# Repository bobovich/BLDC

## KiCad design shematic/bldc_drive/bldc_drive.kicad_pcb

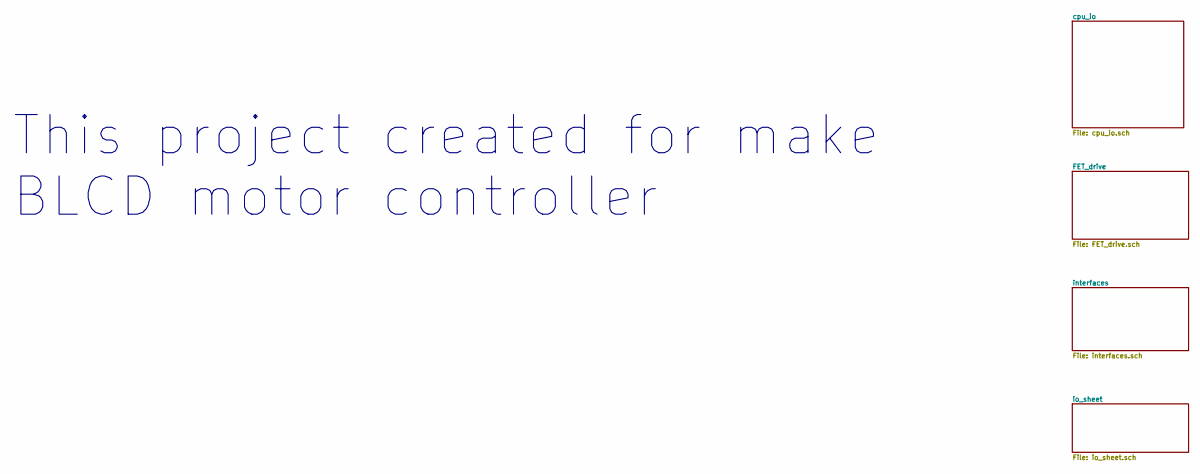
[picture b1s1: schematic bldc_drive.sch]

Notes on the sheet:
This project created for make BLCD motor controller

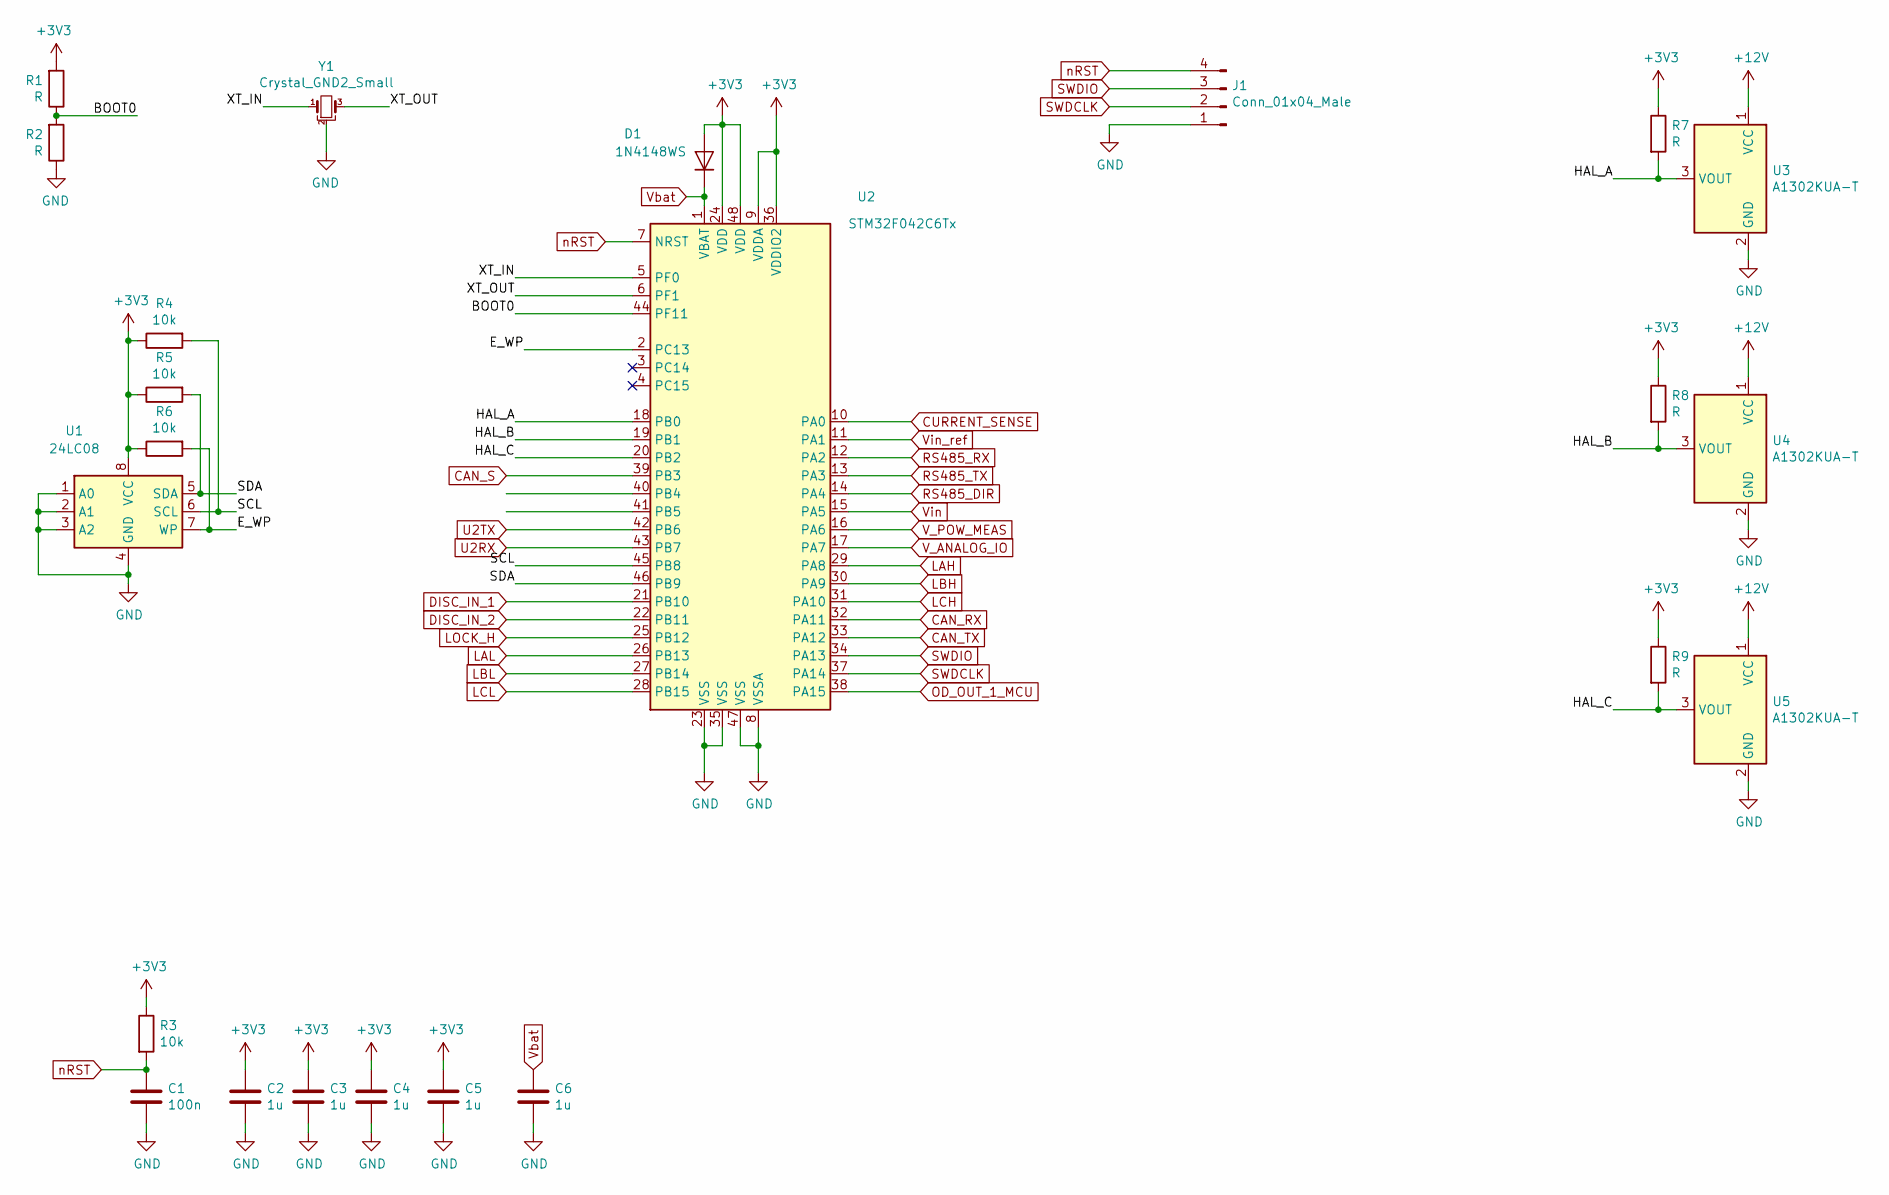
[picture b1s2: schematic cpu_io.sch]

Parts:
C1: 100n; C_0603_1608Metric
C2, C3, C4, C5, C6: 1u; C_0603_1608Metric
D1: 1N4148WS; D_SOD-123
J1: Conn_01x04_Male; PinHeader_1x04_P1.00mm_Vertical
R1, R2, R7, R8, R9: R; R_0603_1608Metric
R3, R4, R5, R6: 10k; R_0603_1608Metric
U1: 24LC08; SOIC-8_3.9x4.9mm_P1.27mm
U2: STM32F042C6Tx; LQFP-48_7x7mm_P0.5mm
U3, U4, U5: A1302KUA-T; TO-92_Wide
Y1: Crystal_GND2_Small; Resonator_SMD_muRata_CSTxExxV-3Pin_3.0x1.1mm

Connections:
+3V3: C2.2, C3.2, C4.2, C5.2, D1.2 (A), R1.2, R3.1, R4.1, R5.1, R6.1, R7.1, R8.1, R9.1, U1.8 (VCC), U2.9 (VDDA), U2.24 (VDD), U2.36 (VDDIO2), U2.48 (VDD); also elsewhere on the board
+12V: U3.1 (VCC), U4.1 (VCC), U5.1 (VCC); also elsewhere on the board
/cpu_io/BOOT0: R1.1, R2.2, U2.44 (PF11)
/cpu_io/E_WP: R6.2, U1.7 (WP), U2.2 (PC13)
/cpu_io/HAL_A: R7.2, U2.18 (PB0), U3.3 (VOUT)
/cpu_io/HAL_B: R8.2, U2.19 (PB1), U4.3 (VOUT)
/cpu_io/HAL_C: R9.2, U2.20 (PB2), U5.3 (VOUT)
/cpu_io/SCL: R4.2, U1.6 (SCL), U2.45 (PB8)
/cpu_io/SDA: R5.2, U1.5 (SDA), U2.46 (PB9)
/cpu_io/XT_IN: U2.5 (PF0), Y1.1
/cpu_io/XT_OUT: U2.6 (PF1), Y1.3
CAN_RX: U2.32 (PA11); also elsewhere on the board
CAN_S: U2.39 (PB3); also elsewhere on the board
CAN_TX: U2.33 (PA12); also elsewhere on the board
CURRENT_SENSE: U2.10 (PA0); also elsewhere on the board
GND: C1.1, C2.1, C3.1, C4.1, C5.1, C6.1, J1.1, R2.1, U1.1 (A0), U1.2 (A1), U1.3 (A2), U1.4 (GND), U2.8 (VSSA), U2.23 (VSS), U2.35 (VSS), U2.47 (VSS), U3.2 (GND), U4.2 (GND), U5.2 (GND), Y1.2; also elsewhere on the board
LAH: U2.29 (PA8); also elsewhere on the board
LAL: U2.26 (PB13); also elsewhere on the board
LBH: U2.30 (PA9); also elsewhere on the board
LBL: U2.27 (PB14); also elsewhere on the board
LCH: U2.31 (PA10); also elsewhere on the board
LCL: U2.28 (PB15); also elsewhere on the board
LOCK_H: U2.25 (PB12); also elsewhere on the board
RS485_DIR: U2.14 (PA4); also elsewhere on the board
RS485_RX: U2.12 (PA2); also elsewhere on the board
RS485_TX: U2.13 (PA3); also elsewhere on the board
SWDCLK: J1.2, U2.37 (PA14)
SWDIO: J1.3, U2.34 (PA13)
U2RX: U2.43 (PB7); also elsewhere on the board
U2TX: U2.42 (PB6); also elsewhere on the board
V_POW_MEAS: U2.16 (PA6); also elsewhere on the board
Vbat: C6.2, D1.1 (K), U2.1 (VBAT)
Vin: U2.15 (PA5); also elsewhere on the board
Vin_ref: U2.11 (PA1); also elsewhere on the board
nRST: C1.2, J1.4, R3.2, U2.7 (NRST)

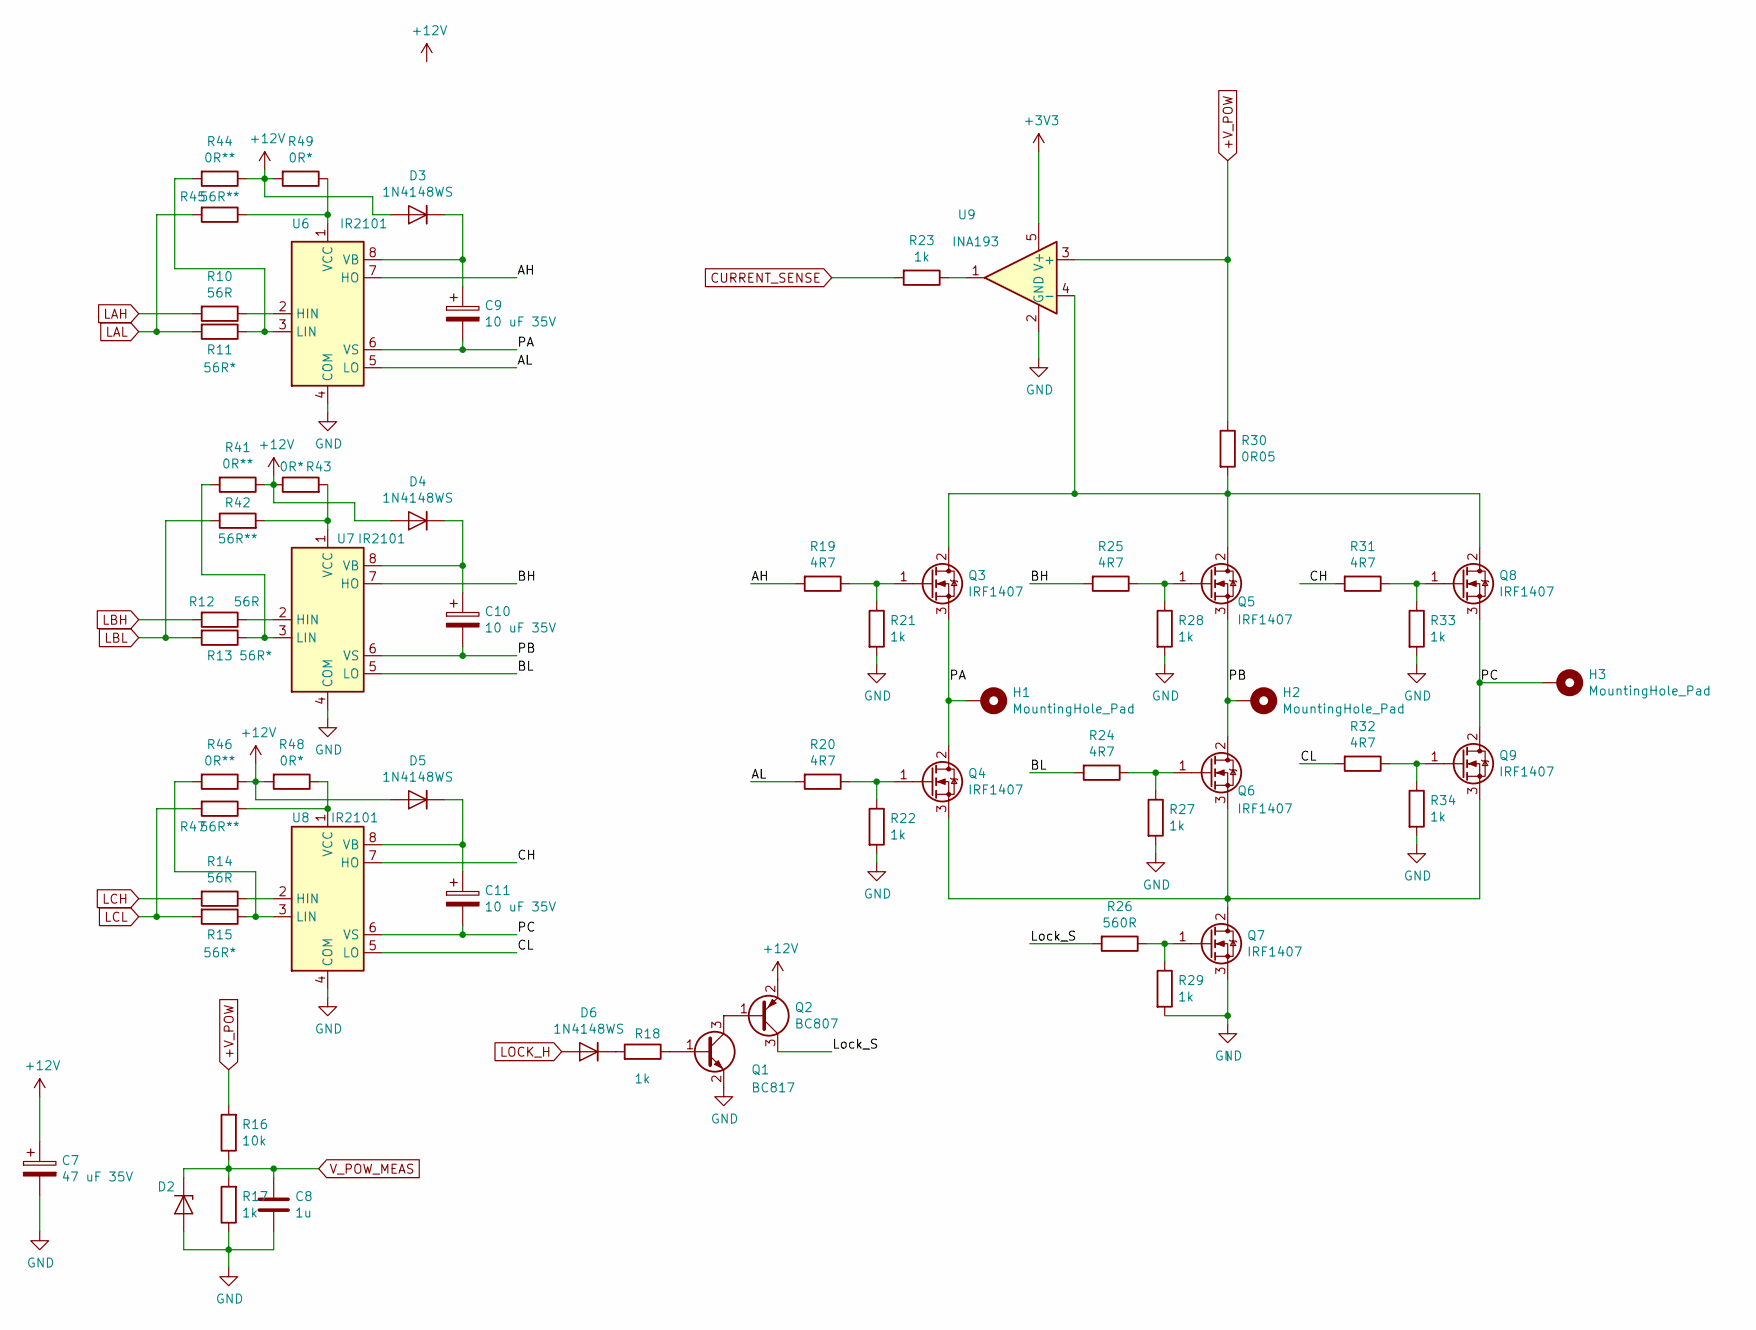
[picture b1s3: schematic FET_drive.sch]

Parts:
C7: 47 uF 35V; C_1206_3216Metric
C8: 1u; C_0805_2012Metric
C9, C10, C11: 10 uF 35V; C_1206_3216Metric
D2: DZ2S033X0L; D_SOD-523
D3, D4, D5, D6: 1N4148WS; D_SOD-123
H1, H2, H3: MountingHole_Pad; MountingHole_6x2
Q1: BC817; SOT-23
Q2: BC807; SOT-23
Q3, Q4, Q5, Q6, Q7, Q8, Q9: IRF1407; TO-220-3_Vertical
R10, R12, R14: 56R; R_0603_1608Metric
R11, R13, R15: 56R*; R_0603_1608Metric
R16: 10k; R_0603_1608Metric
R17, R18, R23: 1k; R_0603_1608Metric
R19, R20, R24, R25, R31, R32: 4R7; R_0805_2012Metric
R21, R22, R27, R28, R29, R33, R34: 1k; R_0805_2012Metric
R26: 560R; R_0805_2012Metric
R30: 0R05; R_4020_10251Metric_Pad1.65x5.30mm_HandSolder
R41, R44, R46: 0R**; R_0603_1608Metric
R42, R45, R47: 56R**; R_0603_1608Metric
R43, R48, R49: 0R*; R_0603_1608Metric
U6, U7, U8: IR2101; SOIC-8_3.9x4.9mm_P1.27mm
U9: INA193; SOT-23-5

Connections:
+3V3: U9.5 (V+); also elsewhere on the board
+12V: C7.1, D3.2 (A), D4.2 (A), D5.2 (A), Q2.2 (E), R41.1, R43.1, R44.1, R46.1, R48.2, R49.2; also elsewhere on the board
+V_POW: R16.2, R30.1, U9.3 (+); also elsewhere on the board
/FET_drive/AH: R19.2, U6.7 (HO)
/FET_drive/AL: R20.2, U6.5 (LO)
/FET_drive/BH: R25.2, U7.7 (HO)
/FET_drive/BL: R24.2, U7.5 (LO)
/FET_drive/CH: R31.2, U8.7 (HO)
/FET_drive/CL: R32.2, U8.5 (LO)
/FET_drive/Lock_S: Q2.3 (C), R26.2
/FET_drive/PA: C9.2, H1.1, Q3.3 (S), Q4.2 (D), U6.6 (VS)
/FET_drive/PB: C10.2, H2.1, Q5.3 (S), Q6.2 (D), U7.6 (VS)
/FET_drive/PC: C11.2, H3.1, Q8.3 (S), Q9.2 (D), U8.6 (VS)
CURRENT_SENSE: R23.2; also elsewhere on the board
GND: C7.2, C8.2, D2.2 (A), Q1.2 (E), Q7.3 (S), R17.1, R21.2, R22.2, R27.2, R28.2, R29.2, R33.2, R34.2, U6.4 (COM), U7.4 (COM), U8.4 (COM), U9.2 (GND); also elsewhere on the board
LAH: R10.2; also elsewhere on the board
LAL: R11.2, R45.2; also elsewhere on the board
LBH: R12.2; also elsewhere on the board
LBL: R13.2, R42.1; also elsewhere on the board
LCH: R14.2; also elsewhere on the board
LCL: R15.2, R47.2; also elsewhere on the board
LOCK_H: D6.2 (A); also elsewhere on the board
unnamed: C9.1, D3.1 (K), U6.8 (VB)
unnamed: C10.1, D4.1 (K), U7.8 (VB)
unnamed: C11.1, D5.1 (K), U8.8 (VB)
unnamed: D6.1 (K), R18.2
unnamed: Q1.1 (B), R18.1
unnamed: Q1.3 (C), Q2.1 (B)
unnamed: Q3.1 (G), R19.1, R21.1
unnamed: Q3.2 (D), Q5.2 (D), Q8.2 (D), R30.2, U9.4 (-)
unnamed: Q4.1 (G), R20.1, R22.1
unnamed: Q4.3 (S), Q6.3 (S), Q7.2 (D), Q9.3 (S)
unnamed: Q5.1 (G), R25.1, R28.1
unnamed: Q6.1 (G), R24.1, R27.1
unnamed: Q7.1 (G), R26.1, R29.1
unnamed: Q8.1 (G), R31.1, R33.1
unnamed: Q9.1 (G), R32.1, R34.1
unnamed: R10.1, U6.2 (HIN)
unnamed: R11.1, R44.2, U6.3 (LIN)
unnamed: R12.1, U7.2 (HIN)
unnamed: R13.1, R41.2, U7.3 (LIN)
unnamed: R14.1, U8.2 (HIN)
unnamed: R15.1, R46.2, U8.3 (LIN)
unnamed: R23.1, U9.1
unnamed: R42.2, R43.2, U7.1 (VCC)
unnamed: R45.1, R49.1, U6.1 (VCC)
unnamed: R47.1, R48.1, U8.1 (VCC)
V_POW_MEAS: C8.1, D2.1 (K), R16.1, R17.2; also elsewhere on the board

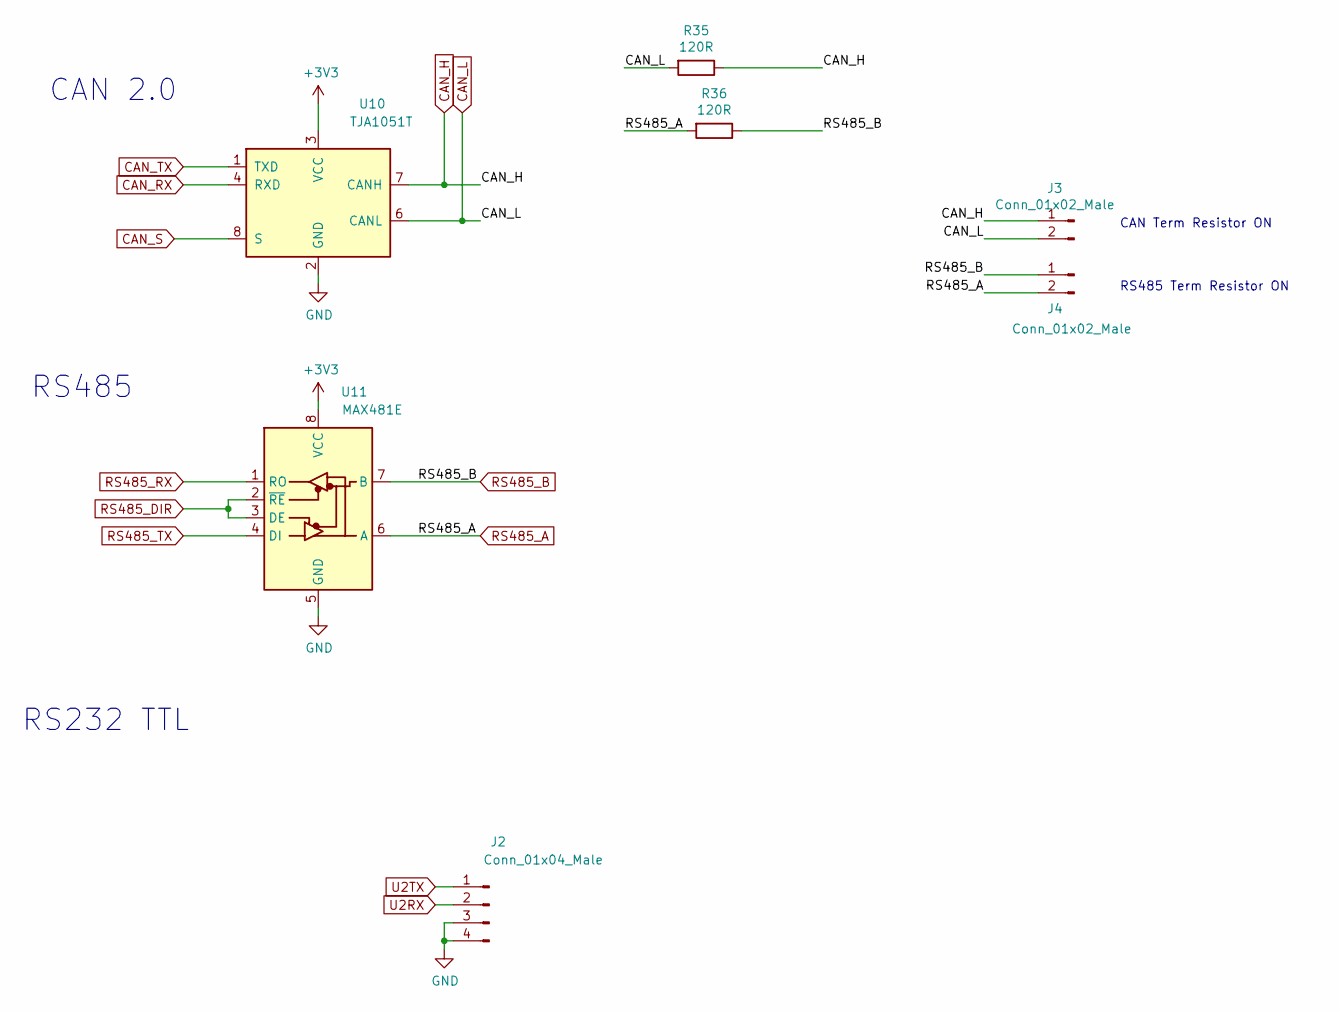
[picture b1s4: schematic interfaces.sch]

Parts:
J2: Conn_01x04_Male; PinHeader_1x04_P1.27mm_Vertical
J3, J4: Conn_01x02_Male; PinHeader_1x02_P2.54mm_Vertical
R35, R36: 120R; R_1206_3216Metric
U10: TJA1051T; SOIC-8_3.9x4.9mm_P1.27mm
U11: MAX481E; SOIC-8_3.9x4.9mm_P1.27mm

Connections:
+3V3: U10.3 (VCC), U11.8 (VCC); also elsewhere on the board
CAN_H: J3.1, R35.1, U10.7 (CANH)
CAN_L: J3.2, R35.2, U10.6 (CANL)
CAN_RX: U10.4 (RXD); also elsewhere on the board
CAN_S: U10.8 (S); also elsewhere on the board
CAN_TX: U10.1 (TXD); also elsewhere on the board
GND: J2.3, J2.4, U10.2 (GND), U11.5 (GND); also elsewhere on the board
RS485_A: J4.2, R36.2, U11.6 (A)
RS485_B: J4.1, R36.1, U11.7 (B)
RS485_DIR: U11.2 (~RE), U11.3 (DE); also elsewhere on the board
RS485_RX: U11.1 (RO); also elsewhere on the board
RS485_TX: U11.4 (DI); also elsewhere on the board
U2RX: J2.2; also elsewhere on the board
U2TX: J2.1; also elsewhere on the board

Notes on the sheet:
CAN Term Resistor ON
RS485 Term Resistor ON
RS232 TTL
RS485
CAN 2.0

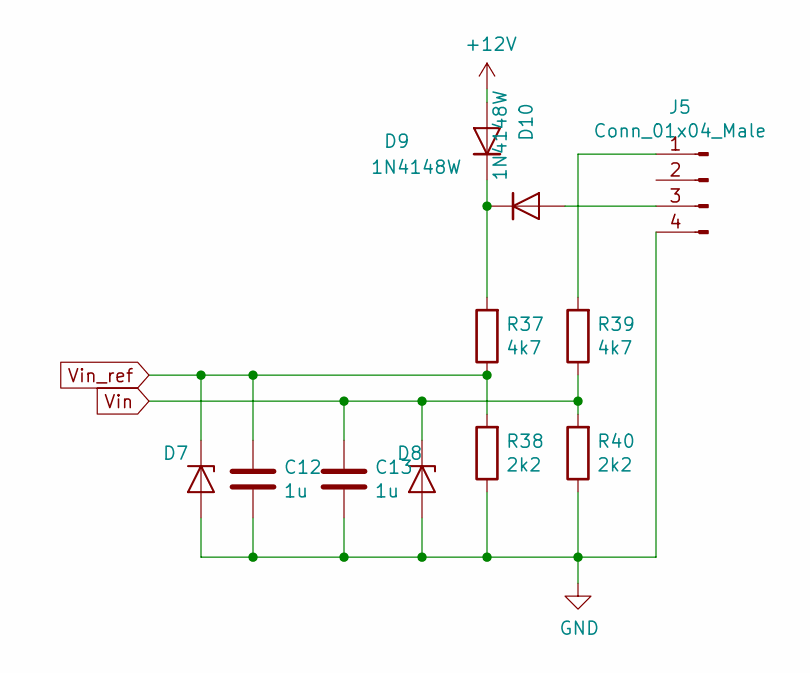
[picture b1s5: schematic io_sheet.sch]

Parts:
C12, C13: 1u; C_0805_2012Metric
D7, D8: DZ2S033X0L; D_SOD-523
D9, D10: 1N4148W; D_SOD-123
J5: Conn_01x04_Male; PinHeader_1x04_P2.54mm_Vertical
R37, R39: 4k7; R_0603_1608Metric
R38, R40: 2k2; R_0603_1608Metric

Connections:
+12V: D9.2 (A); also elsewhere on the board
GND: C12.2, C13.2, D7.2 (A), D8.2 (A), J5.4, R38.1, R40.1; also elsewhere on the board
unnamed: D9.1 (K), D10.1 (K), R37.2
unnamed: D10.2 (A), J5.3
unnamed: J5.1, R39.2
Vin: C13.1, D8.1 (K), R39.1, R40.2; also elsewhere on the board
Vin_ref: C12.1, D7.1 (K), R37.1, R38.2; also elsewhere on the board

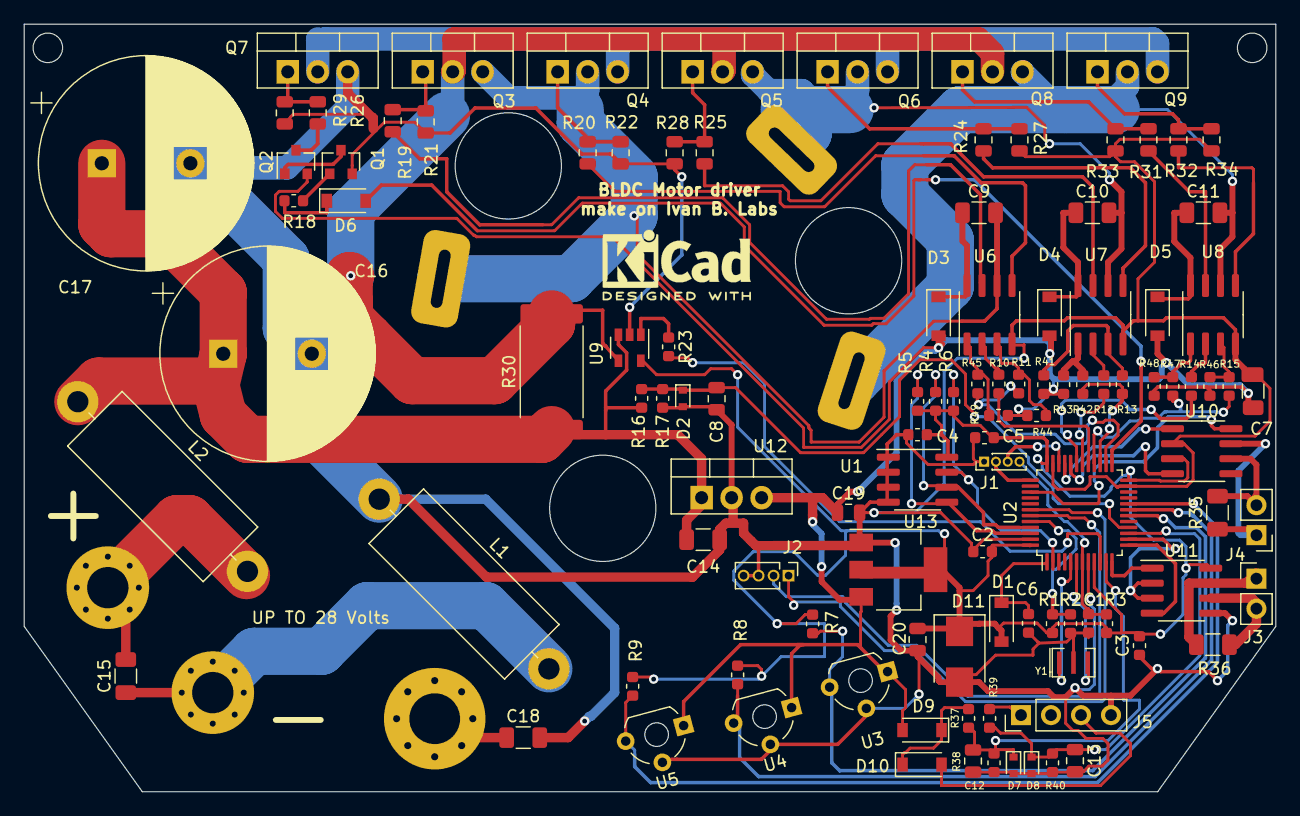
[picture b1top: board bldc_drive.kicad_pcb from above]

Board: 2 copper layers, 106.0 x 65.0 mm, 116 parts (0 on the bottom side), 81 nets.

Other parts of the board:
C14, C18: 1u; C_1206_3216Metric
C15: 2u2; C_1206_3216Metric
C16, C17: 2200uf; CP_Radial_D18.0mm_P7.50mm
C19, C20: C; C_0805_2012Metric
D11: D_Zener; D_SMB
H4, H5: MountingHole_Pad; MountingHole_3.5mm_Pad_Via
H6: MountingHole_Pad; MountingHole_4.3mm_M4_Pad_Via
L1, L2: INDUCTOR; L_Axial_L16.0mm_D6.3mm_P20.32mm_Horizontal_Fastron_VHBCC
U12: uA7812; TO-220-3_Vertical
U13: AP1117-33; SOT-223-3_TabPin2

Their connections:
+3V3: C20.1, D11.1, U13.2; also elsewhere on the board
+12V: C19.1, U12.3, U13.3; also elsewhere on the board
+V_POW: C14.1, C16.1, C17.1, L2.1, U12.1; also elsewhere on the board
GND: C14.2, C16.2, C17.2, C18.2, C19.2, C20.2, D11.2, L1.1, U12.2, U13.1; also elsewhere on the board
unnamed: C15.1, H4.1, L1.2
unnamed: C15.2, H5.1, L2.2
unnamed: C18.1, H6.1

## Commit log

2020-05-01 01.05.2020 22.52 --
2020-05-01 02.05.2020 01.18 --
2020-05-06 06.05.2020 16.54 --
2020-05-10 10.05.2020 21.40 --
2020-05-22 22.05.2020 21.40 --
2020-06-06 03.06.2020 21.40 --
2020-06-11 11.06.2020 21.40 --
2020-08-29 29.08.20
2020-08-30 30.08.20
2020-09-02 replace ir2304 to ir2101
2020-09-07 cut w
2020-09-13 modify for warios drive
